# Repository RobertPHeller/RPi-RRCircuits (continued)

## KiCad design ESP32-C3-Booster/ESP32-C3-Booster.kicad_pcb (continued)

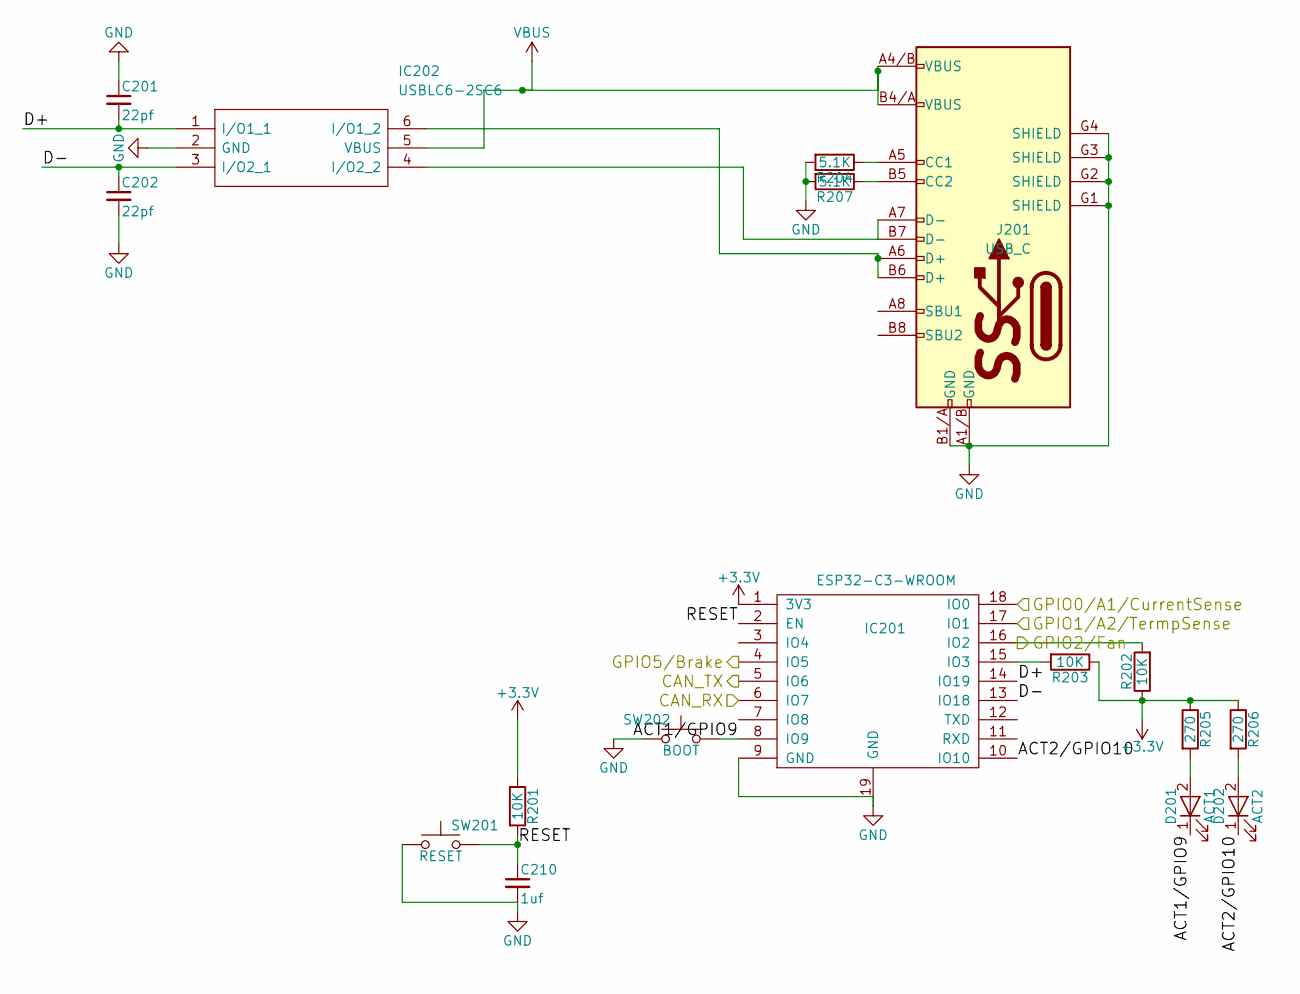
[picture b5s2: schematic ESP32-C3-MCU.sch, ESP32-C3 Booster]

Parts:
C201, C202: 22pf; C_0402; Mouser Part Number 187-CL05C220JB5NNND
C210: 1uf; C_0402; Mouser Part Number 80-C0402C101K8RAUTO
D201: ACT1; LED_0402; Mouser Part Number 710-150040GS73220
D202: ACT2; LED_0402; Mouser Part Number 710-150040SS73220
IC201: ESP32-C3-WROOM; Mouser Part Number 356-ESP32C3WROOM02N4
IC202: USBLC6-2SC6; SOT-23-6; Mouser Part Number 511-USBLC6-2SC6
J201: USB_C; GCT_USB4105-GF-A; Mouser Part Number 640-USB4105-GF-A-120
R201, R202, R203: 10K; R_0402; Mouser Part Number 603-RC0402JR-1310KL
R204, R207: 5.1K; R_0402; Mouser Part Number 71-CRCW0402-5.1K-E3
R205, R206: 270; R_0402; Mouser Part Number 754-RR0510P-271D
SW201: RESET; PTS647SM38SMTR2LFS; Mouser Part Number 611-PTS647SN70SMTR2L
SW202: BOOT; PTS647SM38SMTR2LFS; Mouser Part Number 611-PTS647SN70SMTR2L

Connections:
+3V3: IC201.1 (3V3), R201.1, R202.1, R203.1, R205.1, R206.1; also elsewhere on the board
/CAN Transeiver/CAN_RX: IC201.6 (IO7); also elsewhere on the board
/CAN Transeiver/CAN_TX: IC201.5 (IO6); also elsewhere on the board
/ESP32-C3 MCU/ACT1/GPIO9: D201.1 (K), IC201.8 (IO9), SW202.1
/ESP32-C3 MCU/ACT2/GPIO10: D202.1 (K), IC201.10 (IO10)
/ESP32-C3 MCU/D+: C201.2, IC201.14 (IO19), IC202.1 (I/O1_1)
/ESP32-C3 MCU/D-: C202.1, IC201.13 (IO18), IC202.3 (I/O2_1)
/ESP32-C3 MCU/GPIO0/A1/CurrentSense: IC201.18 (IO0); also elsewhere on the board
/ESP32-C3 MCU/GPIO1/A2/TermpSense: IC201.17 (IO1); also elsewhere on the board
/ESP32-C3 MCU/RESET: C210.1, IC201.2 (EN), R201.2, SW201.2
/Fan Controls/FAN_CONTROL: IC201.16 (IO2), R202.2; also elsewhere on the board
/OPS Driver/BRAKE: IC201.4 (IO5); also elsewhere on the board
GND: C201.1, C202.2, C210.2, IC201.9 (GND), IC201.19 (GND), IC202.2 (GND), J201.A1/B (GND), J201.B1/A (GND), J201.G1 (SHIELD), J201.G2 (SHIELD), J201.G3 (SHIELD), J201.G4 (SHIELD), R204.2, R207.2, SW201.1, SW202.2; also elsewhere on the board
unnamed: D201.2 (A), R205.2
unnamed: D202.2 (A), R206.2
unnamed: IC201.15 (IO3), R203.2
unnamed: IC202.4 (I/O2_2), J201.A7 (D-), J201.B7 (D-)
unnamed: IC202.6 (I/O1_2), J201.A6 (D+), J201.B6 (D+)
unnamed: J201.A5 (CC1), R204.1
unnamed: J201.B5 (CC2), R207.1
VBUS: IC202.5 (VBUS), J201.A4/B (VBUS), J201.B4/A (VBUS); also elsewhere on the board

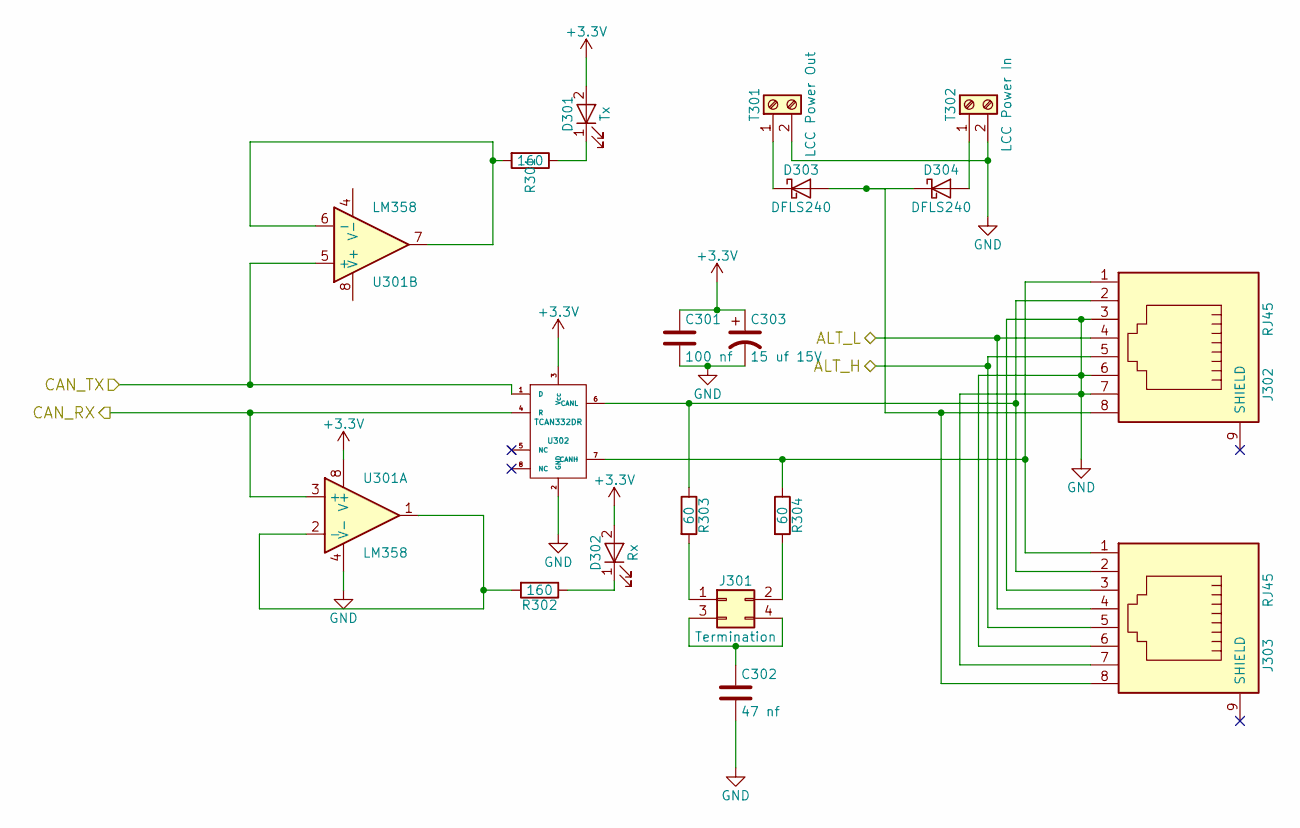
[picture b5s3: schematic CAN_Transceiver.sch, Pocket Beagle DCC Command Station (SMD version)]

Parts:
C301: 100 nf; C_0603; Mouser Part Number 603-CC603KPX7R9BB104
C302: 47 nf; C_0603; Mouser Part Number 963-GMK107BJ473KAHT
C303: 15 uf 15V; CP_Elec_4x5.8; Mouser Part Number 647-UUD1C150MCL
D301: Tx; LED_0603; Mouser Part Number 710-150060SS75000
D302: Rx; LED_0603; Mouser Part Number 710-150060YS75000
D303, D304: DFLS240; D_PowerDI-123; Mouser Part Number 621-DFLS240-7
J301: Termination; Pin_Header_Straight_2x02_Pitch2.54mm; Mouser Part Number 538-90131-0122
J302, J303: RJ45; RJ45_8N-S; Mouser Part Number 710-615008144221
R301, R302: 160; R_0603; Mouser Part Number 603-AC0603JR-07160RL
R303, R304: 60; R_1206; Mouser Part Number 71-CRCW120660R0KNAIF
T301: LCC Power Out; TerminalBlock_Pheonix_MPT-2.54mm_2pol; Mouser Part Number 651-1725656
T302: LCC Power In; TerminalBlock_Pheonix_MPT-2.54mm_2pol; Mouser Part Number 651-1725656
U301: LM358; SOIC-8_3.9x4.9mm_Pitch1.27mm; Mouser Part Number 595-LM358BIDR
U302: TCAN332DR; SOIC-8_3.9x4.9mm_Pitch1.27mm; Mouser Part Number 595-TCAN332DR

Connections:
+3V3: C301.1, C303.1, D301.2 (A), D302.2 (A), U301.8 (V+), U302.3 (Vcc); also elsewhere on the board
/CAN Transeiver/ALT_H: J302.5, J303.5; also elsewhere on the board
/CAN Transeiver/ALT_L: J302.4, J303.4; also elsewhere on the board
/CAN Transeiver/CAN_RX: U301.3 (+), U302.4 (R); also elsewhere on the board
/CAN Transeiver/CAN_TX: U301.5 (+), U302.1 (D); also elsewhere on the board
GND: C301.2, C302.2, C303.2, J302.3, J302.6, J302.7, J303.3, J303.6, J303.7, T301.2, T302.2, U301.4 (V-), U302.2 (GND); also elsewhere on the board
unnamed: C302.1, J301.3, J301.4
unnamed: D301.1 (K), R301.1
unnamed: D302.1 (K), R302.1
unnamed: D303.1 (K), T301.1
unnamed: D303.2 (A), D304.1 (K), J302.8, J303.8
unnamed: D304.2 (A), T302.1
unnamed: J301.1, R303.2
unnamed: J301.2, R304.2
unnamed: J302.1, J303.1, R304.1, U302.7 (CANH)
unnamed: J302.2, J303.2, R303.1, U302.6 (CANL)
unnamed: R301.2, U301.6 (-), U301.7
unnamed: R302.2, U301.1, U301.2 (-)

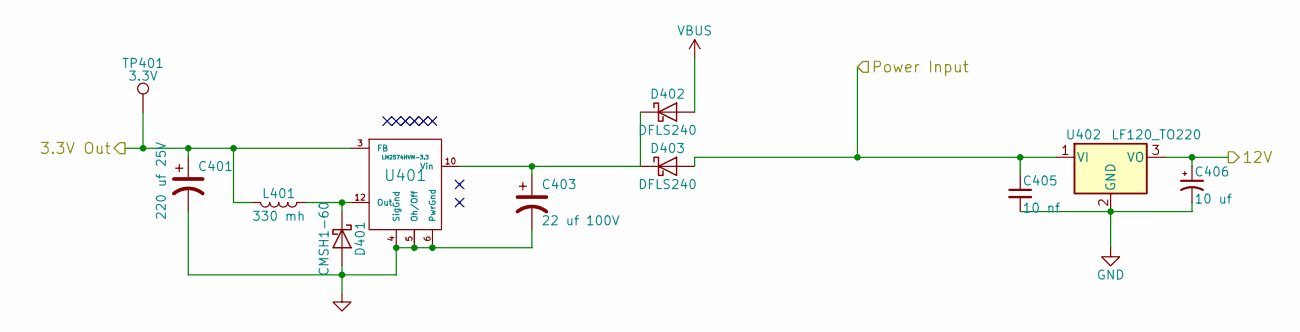
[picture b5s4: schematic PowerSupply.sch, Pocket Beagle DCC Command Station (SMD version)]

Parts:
C401: 220 uf 25V; CP_Elec_8x10; Mouser Part Number 647-UUX2A220MNL6GS
C403: 22 uf 100V; CP_Elec_8x10; Mouser Part Number 647-UWT1E221MNL1GS
C405: 10 nf; C_1206; Mouser Part Number 791-1206B103K500CT
C406: 10 uf; CP_Elec_5x5.3; Mouser Part Number 710-865230542002
D401: CMSH1-60; D_SMA; Mouser Part Number 610-CMSH1-60TR13
D402, D403: DFLS240; D_PowerDI-123; Mouser Part Number 621-DFLS240-7
L401: 330 mh; SRN1060; Mouser Part Number 652-SRN1060-331M
TP401: 3.3V; Measurement_Point_Round-SMD-Pad_Big
U401: LM2574HVM-3.3; SOIC-14_7.4x8.7mm_Pitch1.27mm; Mouser Part Number 926-LM2574MX33NOPB
U402: LF120_TO220; TO-252-2; Mouser Part Number 511-LF120ABDT-TR

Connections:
+3V3: C401.1, L401.2, TP401.1, U401.3 (FB); also elsewhere on the board
+12V: C406.1, U402.3 (VO); also elsewhere on the board
/Power Supply/Power Input: C405.1, D403.2 (A), U402.1 (VI); also elsewhere on the board
GND: C401.2, C403.2, C405.2, C406.2, D401.2 (A), U401.4 (SigGnd), U401.5 (Oh/Off), U401.6 (PwrGnd), U402.2 (GND); also elsewhere on the board
unnamed: C403.1, D402.1 (K), D403.1 (K), U401.10 (Vin)
unnamed: D401.1 (K), L401.1, U401.12 (Out)
VBUS: D402.2 (A); also elsewhere on the board

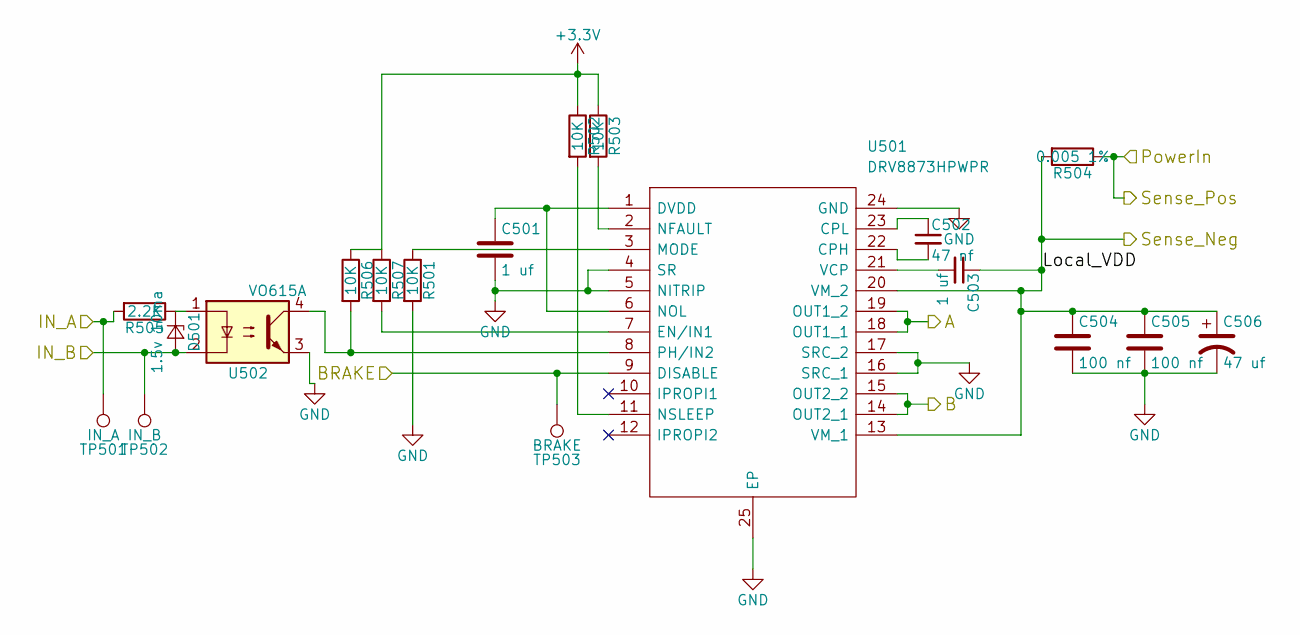
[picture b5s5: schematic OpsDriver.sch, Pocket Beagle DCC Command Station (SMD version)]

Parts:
C501, C503: 1 uf; C_0603; Mouser Part Number 963-GMK107AB7105KAHT
C502: 47 nf; C_0603; Mouser Part Number 963-GMK107BJ473KAHT
C504, C505: 100 nf; C_0603; Mouser Part Number 603-CC603KPX7R9BB104
C506: 47 uf; CP_Elec_6.3x5.3; Mouser Part Number 710-865080543009
D501: 1.5v 10ma; D_SOD-323; Mouser Part Number 610-CMDZ1L8TR
R501, R502, R503, R506, R507: 10K; R_0603; Mouser Part Number 279-CRGCQ0603F10K
R504: 0.005 1%; R_0612; Mouser Part Number 71-WSKW0612L5000FEA
R505: 2.2K; R_0603; Mouser Part Number 603-AC0603FR-072K2L
TP501: IN_A; Measurement_Point_Round-SMD-Pad_Big
TP502: IN_B; Measurement_Point_Round-SMD-Pad_Big
TP503: BRAKE; Measurement_Point_Round-SMD-Pad_Big
U501: DRV8873HPWPR; SOP65P640X120-25N; Mouser Part Number 595-DRV8873HPWPR
U502: VO615A; SO-4_7.6x3.6mm_Pitch2.54mm; Mouser Part Number 78-VO615A-7X017T

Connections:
+3V3: R502.1, R503.1, R506.1, R507.1; also elsewhere on the board
/CAN Transeiver/ALT_H: R505.2, TP501.1; also elsewhere on the board
/CAN Transeiver/ALT_L: D501.2 (A), TP502.1, U502.2; also elsewhere on the board
/OPS Driver/A: U501.18 (OUT1_1), U501.19 (OUT1_2); also elsewhere on the board
/OPS Driver/B: U501.14 (OUT2_1), U501.15 (OUT2_2); also elsewhere on the board
/OPS Driver/BRAKE: TP503.1, U501.9 (DISABLE); also elsewhere on the board
/OPS Driver/Sense_Neg: C503.1, C504.1, C505.1, C506.1, R504.2, U501.13 (VM_1), U501.20 (VM_2); also elsewhere on the board
/Power Supply/Power Input: R504.1; also elsewhere on the board
GND: C501.2, C504.2, C505.2, C506.2, R501.2, U501.4 (SR), U501.5 (NITRIP), U501.16 (SRC_1), U501.17 (SRC_2), U501.24 (GND), U501.25 (EP), U502.3; also elsewhere on the board
unnamed: C501.1, U501.1 (DVDD), U501.6 (NOL)
unnamed: C502.1, U501.23 (CPL)
unnamed: C502.2, U501.22 (CPH)
unnamed: C503.2, U501.21 (VCP)
unnamed: D501.1 (K), R505.1, U502.1
unnamed: R501.1, U501.3 (MODE)
unnamed: R502.2, U501.11 (NSLEEP)
unnamed: R503.2, U501.2 (NFAULT)
unnamed: R506.2, U501.8 (PH/IN2), U502.4
unnamed: R507.2, U501.7 (EN/IN1)

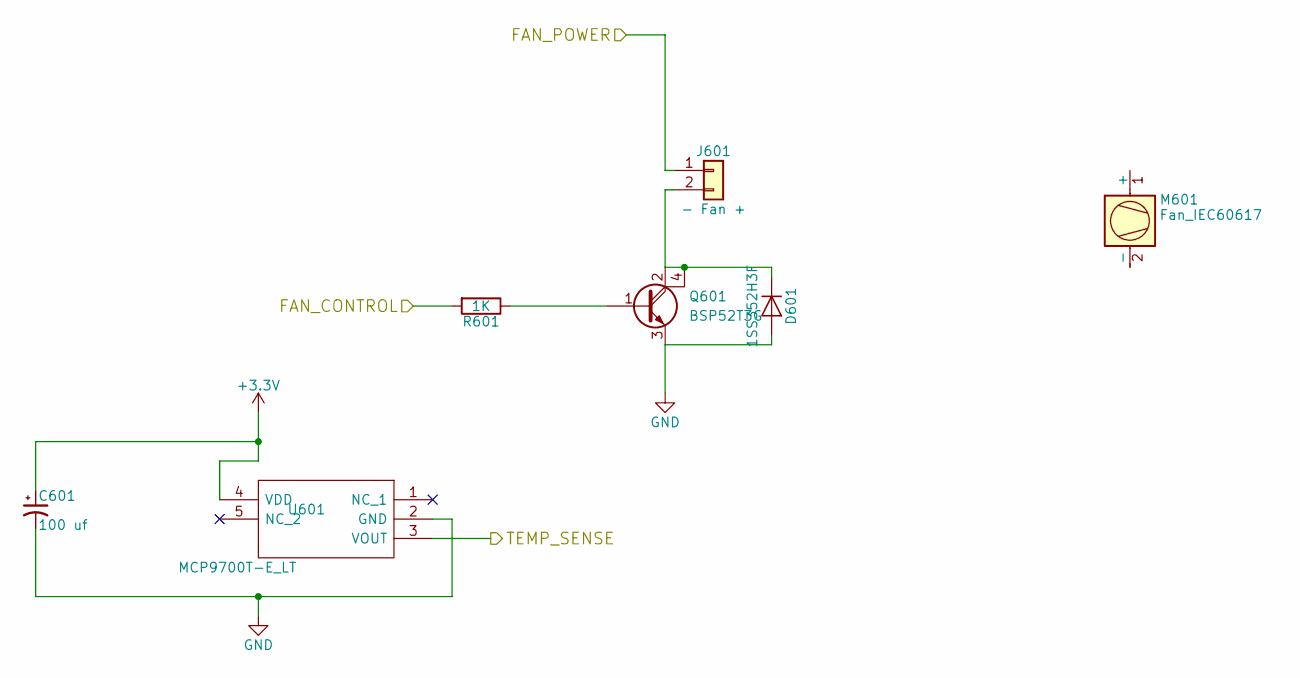
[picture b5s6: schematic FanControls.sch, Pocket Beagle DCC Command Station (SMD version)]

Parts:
C601: 100 uf; C_0603; Mouser Part Number 603-CC603KPX7R9BB104
D601: 1SS352H3F; D_SOD-323; Mouser Part Number 757-1SS352H3F
J601: - Fan +; Pin_Header_Straight_1x02_Pitch2.54mm; Mouser Part Number 538-42375-1855
M601: Fan_IEC60617; 25mmFanMount; Mouser Part Number 490-CFM2510B1100-218
Q601: BSP52T3G; SOT-223; Mouser Part Number 863-BSP52T3G
R601: 1K; R_0603; Mouser Part Number 279-CRGCQ0603F1K0
U601: MCP9700T-E_LT; SOT65P210X110-5N; Mouser Part Number 579-MCP9700T-E/LT

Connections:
+3V3: C601.1, U601.4 (VDD); also elsewhere on the board
+12V: J601.1; also elsewhere on the board
/ESP32-C3 MCU/GPIO1/A2/TermpSense: U601.3 (VOUT); also elsewhere on the board
/Fan Controls/FAN_CONTROL: R601.2; also elsewhere on the board
GND: C601.2, D601.2 (A), Q601.3 (E), U601.2 (GND); also elsewhere on the board
unnamed: D601.1 (K), J601.2, Q601.2 (C), Q601.4 (C2)
unnamed: Q601.1 (B), R601.1

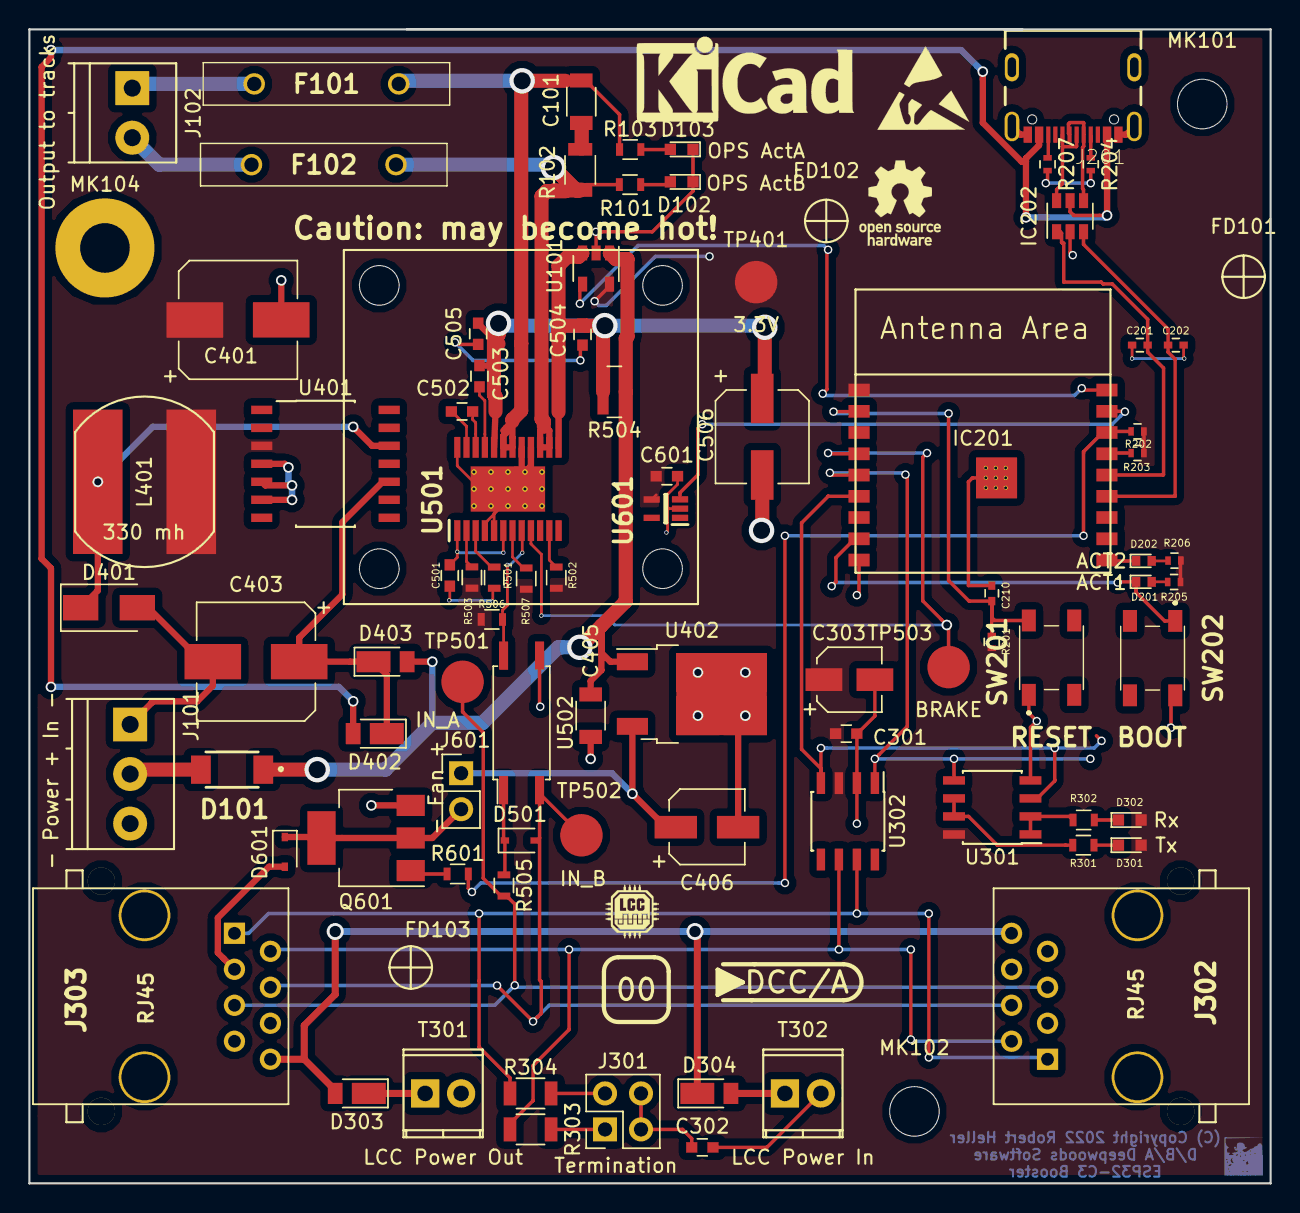
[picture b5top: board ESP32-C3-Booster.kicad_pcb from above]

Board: 2 copper layers, 87.6 x 81.5 mm, 90 parts (0 on the bottom side), 60 nets.

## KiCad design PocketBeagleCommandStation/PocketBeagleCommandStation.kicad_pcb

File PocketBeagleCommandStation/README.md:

# PocketBeagleCommandStation

Through hole version of the PocketBeagle LCC/DCC Command Station. This is a
DCC command station that is a LCC node. It implements the OpenLCB train
protocol node over LCC and converts that to DCC commands. It includes a
booster and puts the DCC signal on the LCC bus (pins 4 and 5). It implements a
programming track and implements Railcom. The Command Station uses a
PocketBeagle as the processing element and uses the PRUs (Programmable
Realtime Units) to generate the DCC signal. (See
[PocketBeagleCommandStation_SMD](https://github.com/RobertPHeller/RPi-RRCircuits/tree/master/PocketBeagleCommandStation_SMD)
for a SMD version.)

* [Mouser Cart](https://www.mouser.com/ProjectManager/ProjectDetail.aspx?AccessID=514917dd80)
* [Schematic PDF](https://github.com/RobertPHeller/RPi-RRCircuits/blob/master/PocketBeagleCommandStation/PocketBeagleCommandStation.pdf)
* [Board Rendering](https://github.com/RobertPHeller/RPi-RRCircuits/blob/master/PocketBeagleCommandStation/PocketBeagleCommandStation.png)
* [Node Software](https://github.com/RobertPHeller/RPi-RRCircuits/tree/master/BBBCommandStationOpenMRN)
* [Kit Booklet](https://github.com/RobertPHeller/RPi-RRCircuits/blob/master/PocketBeagleCommandStation/KitBooklet.pdf)
* Heat sink files:
  * [Main panel](https://github.com/RobertPHeller/RPi-RRCircuits/blob/master/PocketBeagleCommandStation/HeatSinkMainPanel.pdf)
  * [Fin 1](https://github.com/RobertPHeller/RPi-RRCircuits/blob/master/PocketBeagleCommandStation/HeatSinkFin1Panel.pdf)
  * [Fin 2](https://github.com/RobertPHeller/RPi-RRCircuits/blob/master/PocketBeagleCommandStation/HeatSinkFin2Panel.pdf)
  * [Cut page 1:1 (SVG)](https://github.com/RobertPHeller/RPi-RRCircuits/blob/master/PocketBeagleCommandStation/HeatSinkLaserCutPage-nocps-cutsonly.svg)
  * [Cut and bend 1:1 (SVG)](https://github.com/RobertPHeller/RPi-RRCircuits/blob/master/PocketBeagleCommandStation/HeatSinkLaserCutPage-nocps.svg)
  * [Cut and bend 1:1 (SVG, with center points)](https://github.com/RobertPHeller/RPi-RRCircuits/blob/master/PocketBeagleCommandStation/HeatSinkLaserCutPage.svg)
  * [FreeCAD Python script](https://github.com/RobertPHeller/RPi-RRCircuits/blob/master/PocketBeagleCommandStation/HeatSink.py)

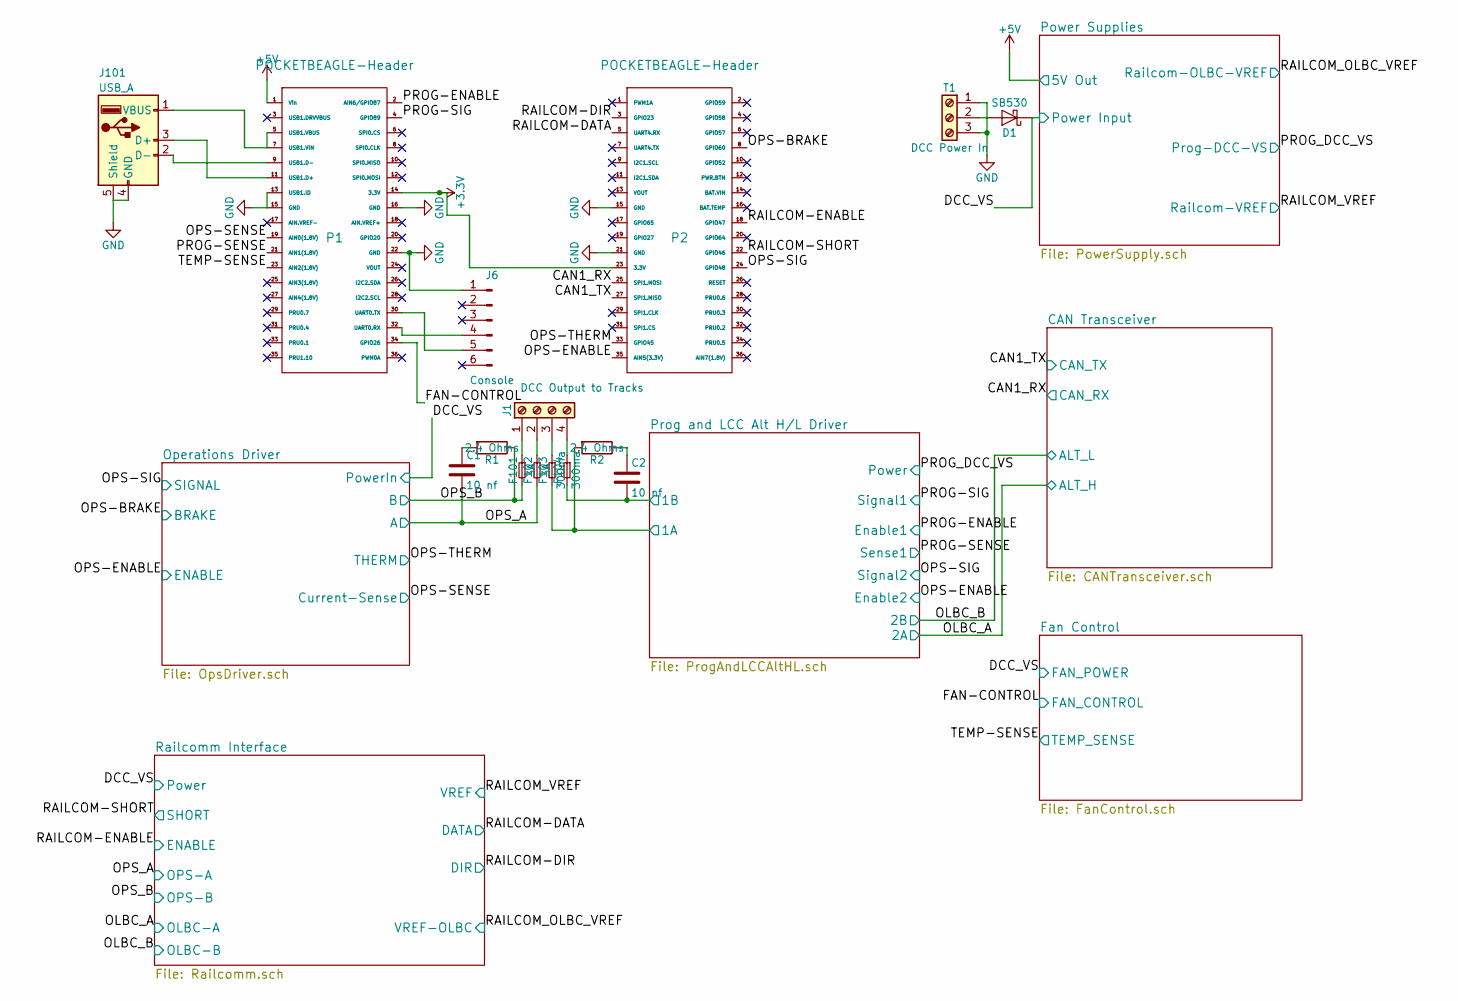
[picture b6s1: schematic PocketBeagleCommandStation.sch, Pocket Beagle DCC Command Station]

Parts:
C1, C2: 10 nf; C_Rect_L4.0mm_W2.5mm_P2.50mm; Mouser Part Number 75-1C10Z5U103M100B
D1: SB530; D_DO-201AD_P12.70mm_Horizontal; Mouser Part Number 625-SB530-E3
F101, F102: 3A; Fuse_BelFuse_0ZRE0033FF_L11.4mm_W3.8mm; Mouser Part Number 530-0ZRB0300FF1A
F103, F104: 300ma; Fuse_Bourns_MF-RG300; Mouser Part Number 530-0ZRC0030FF1E
J1: DCC Output to Tracks; TerminalBlock_Pheonix_PT-3.5mm_4pol; Mouser Part Number 651-5442264
J6: Console; Pin_Header_Straight_1x06_Pitch2.54mm; Mouser Part Number 523-G800W302018EU
J101: USB_A; USB-A-UPRIGHT; Mouser Part Number 710-614004184726
P1, P2: POCKETBEAGLE-Header; Socket_Strip_Straight_2x18_Pitch2.54mm; Mouser Part Number 517-929975-01-18-RK
R1, R2: 2.4 Ohms; R_Axial_DIN0204_L3.6mm_D1.6mm_P2.54mm_Vertical; Mouser Part Number 603-CFR-25JB-52-2R4
T1: DCC Power In; TerminalBlock_Pheonix_PT-3.5mm_3pol; Mouser Part Number 651-5442251

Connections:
+3V3: P1.14 (3.3V), P2.23 (3.3V); also elsewhere on the board
+5V: P1.1 (Vin); also elsewhere on the board
/CAN1_RX: P2.25 (SPI1.MOSI); also elsewhere on the board
/CAN1_TX: P2.27 (SPI1.MISO); also elsewhere on the board
/DCC_VS: D1.1 (K); also elsewhere on the board
/FAN-CONTROL: P1.34 (GPIO26); also elsewhere on the board
/OPS-BRAKE: P2.8 (GPIO60); also elsewhere on the board
/OPS-ENABLE: P2.35 (AIN5(3.3V)); also elsewhere on the board
/OPS-SENSE: P1.19 (AIN0(1.8V)); also elsewhere on the board
/OPS-SIG: P2.24 (GPIO48); also elsewhere on the board
/OPS-THERM: P2.33 (GPIO45); also elsewhere on the board
/OPS_A: C1.2, F102.2; also elsewhere on the board
/OPS_B: F101.2, R1.1; also elsewhere on the board
/PROG-ENABLE: P1.2 (AIN6/GPIO87); also elsewhere on the board
/PROG-SENSE: P1.21 (AIN1(1.8V)); also elsewhere on the board
/PROG-SIG: P1.4 (GPIO89); also elsewhere on the board
/Prog and LCC Alt H/L Driver/1A: F103.2, R2.2; also elsewhere on the board
/Prog and LCC Alt H/L Driver/1B: C2.2, F104.2; also elsewhere on the board
/RAILCOM-DATA: P2.5 (UART4.RX); also elsewhere on the board
/RAILCOM-DIR: P2.3 (GPIO23); also elsewhere on the board
/RAILCOM-ENABLE: P2.18 (GPIO47); also elsewhere on the board
/RAILCOM-SHORT: P2.22 (GPIO46); also elsewhere on the board
/TEMP-SENSE: P1.23 (AIN2(1.8V)); also elsewhere on the board
GND: J6.1, J101.4 (GND), J101.5 (Shield), P1.13 (USB1.ID), P1.15 (GND), P1.16 (GND), P1.22 (GND), P2.15 (GND), P2.21 (GND), T1.1, T1.3; also elsewhere on the board
unnamed: C1.1, R1.2
unnamed: C2.1, R2.1
unnamed: D1.2 (A), T1.2
unnamed: F101.1, J1.1
unnamed: F102.1, J1.2
unnamed: F103.1, J1.3
unnamed: F104.1, J1.4
unnamed: J6.4, P1.32 (UART0.RX)
unnamed: J6.5, P1.30 (UART0.TX)
unnamed: J101.1 (VBUS), P1.5 (USB1.VBUS), P1.7 (USB1.VIN)
unnamed: J101.2 (D-), P1.9 (USB1.D-)
unnamed: J101.3 (D+), P1.11 (USB1.D+)

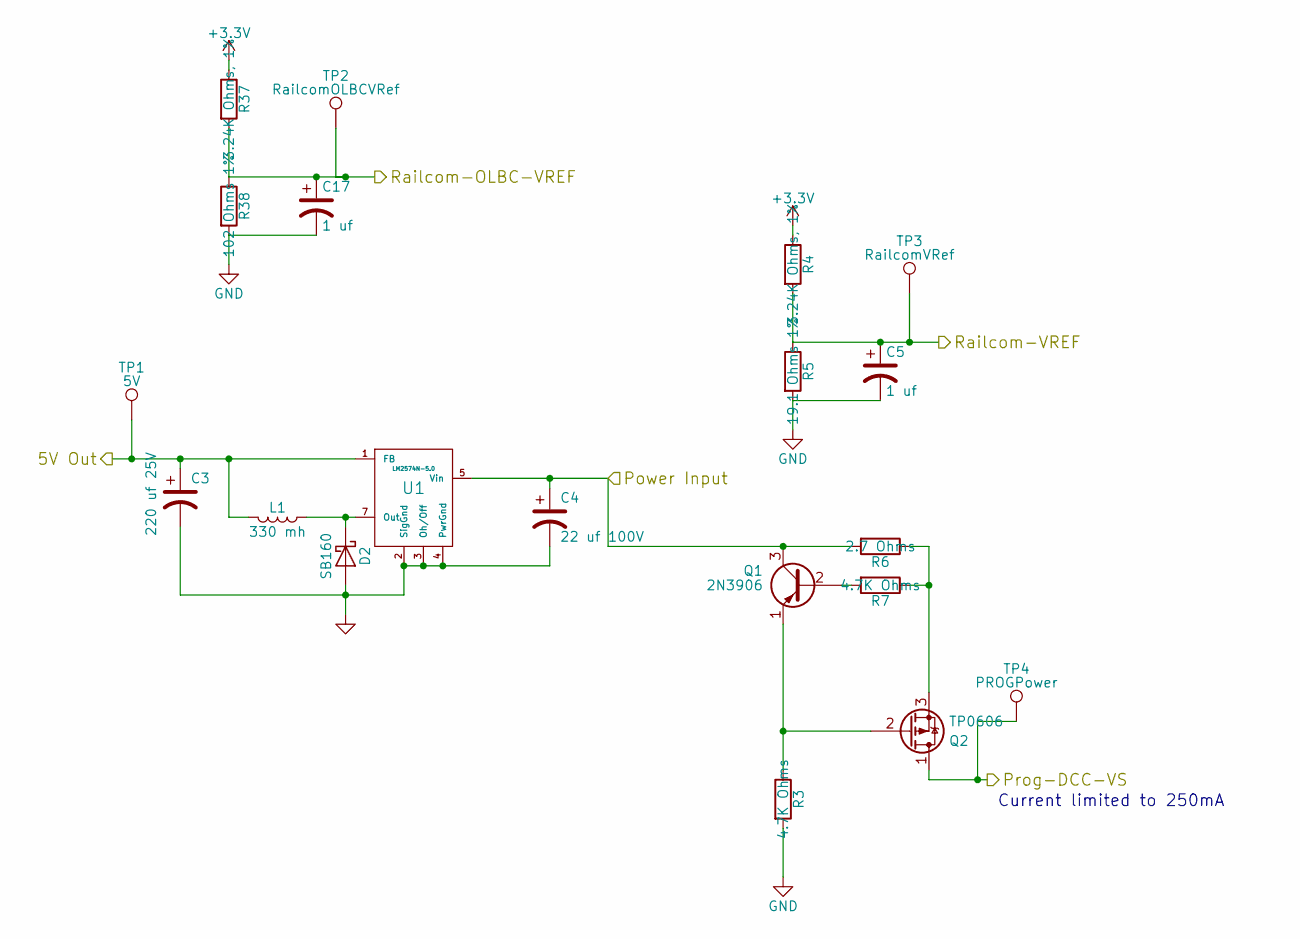
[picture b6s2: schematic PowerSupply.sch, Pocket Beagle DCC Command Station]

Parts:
C3: 220 uf 25V; CP_Radial_D8.0mm_P3.50mm; Mouser Part Number 710-860080474010
C4: 22 uf 100V; CP_Radial_D8.0mm_P3.50mm; Mouser Part Number 667-ECA-1VM220I
C5, C17: 1 uf; CP_Radial_D5.0mm_P2.50mm; Mouser Part Number 810-FG18X5R1H105KRT6
D2: SB160; D_DO-41_SOD81_P7.62mm_Horizontal; Mouser Part Number 750-SB160E-G
L1: 330 mh; PE-LowProfile; Mouser Part Number 673-PE-52627NL
Q1: 2N3906; TO-92_Molded_Narrow; Mouser Part Number 750-2N3906-G
Q2: TP0606; TO-92_Molded_Narrow; Mouser Part Number 689-TP0606N3-G
R3, R7: 4.7K Ohms; R_Axial_DIN0204_L3.6mm_D1.6mm_P2.54mm_Vertical; Mouser Part Number 603-CFR-12JT-52-4K7
R4: 3.24K Ohms, 1%; R_Axial_DIN0204_L3.6mm_D1.6mm_P2.54mm_Vertical; Mouser Part Number 603-MFR-25FRF52-3K24
R5: 19.1 Ohms 1%; R_Axial_DIN0204_L3.6mm_D1.6mm_P2.54mm_Vertical; Mouser Part Number 603-MFR-25FBF52-19R1
R6: 2.7 Ohms; R_Axial_DIN0204_L3.6mm_D1.6mm_P2.54mm_Vertical; Mouser Part Number 603-CFR-25JR-52-2R7
R37: 3.24K Ohms, 1%; R_Axial_DIN0204_L3.6mm_D1.6mm_P1.90mm_Vertical; Mouser Part Number 603-MFR-25FRF52-3K24
R38: 102 Ohms 1%; R_Axial_DIN0204_L3.6mm_D1.6mm_P1.90mm_Vertical; Mouser Part Number 603-MFR-25FBF52-102R
TP1: 5V; Measurement_Point_Round-TH_Small
TP2: RailcomOLBCVRef; Measurement_Point_Round-TH_Small
TP3: RailcomVRef; Measurement_Point_Round-TH_Small
TP4: PROGPower; Measurement_Point_Round-TH_Small
U1: LM2574N-5.0; DIP-8_W7.62mm; Mouser Part Number 926-LM2574N-5.0/NOPB

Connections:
+3V3: R4.1, R37.1; also elsewhere on the board
+5V: C3.1, L1.2, TP1.1, U1.1 (FB); also elsewhere on the board
/DCC_VS: C4.1, Q1.3 (C), R6.2, U1.5 (Vin); also elsewhere on the board
/PROG_DCC_VS: Q2.1 (D), TP4.1; also elsewhere on the board
/RAILCOM_OLBC_VREF: C17.1, R37.2, R38.1, TP2.1; also elsewhere on the board
/RAILCOM_VREF: C5.1, R4.2, R5.1, TP3.1; also elsewhere on the board
GND: C3.2, C4.2, C5.2, C17.2, D2.2 (A), R3.2, R5.2, R38.2, U1.2 (SigGnd), U1.3 (Oh/Off), U1.4 (PwrGnd); also elsewhere on the board
unnamed: D2.1 (K), L1.1, U1.7 (Out)
unnamed: Q1.1 (E), Q2.2 (G), R3.1
unnamed: Q1.2 (B), R7.2
unnamed: Q2.3 (S), R6.1, R7.1

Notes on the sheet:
Current limited to 250mA

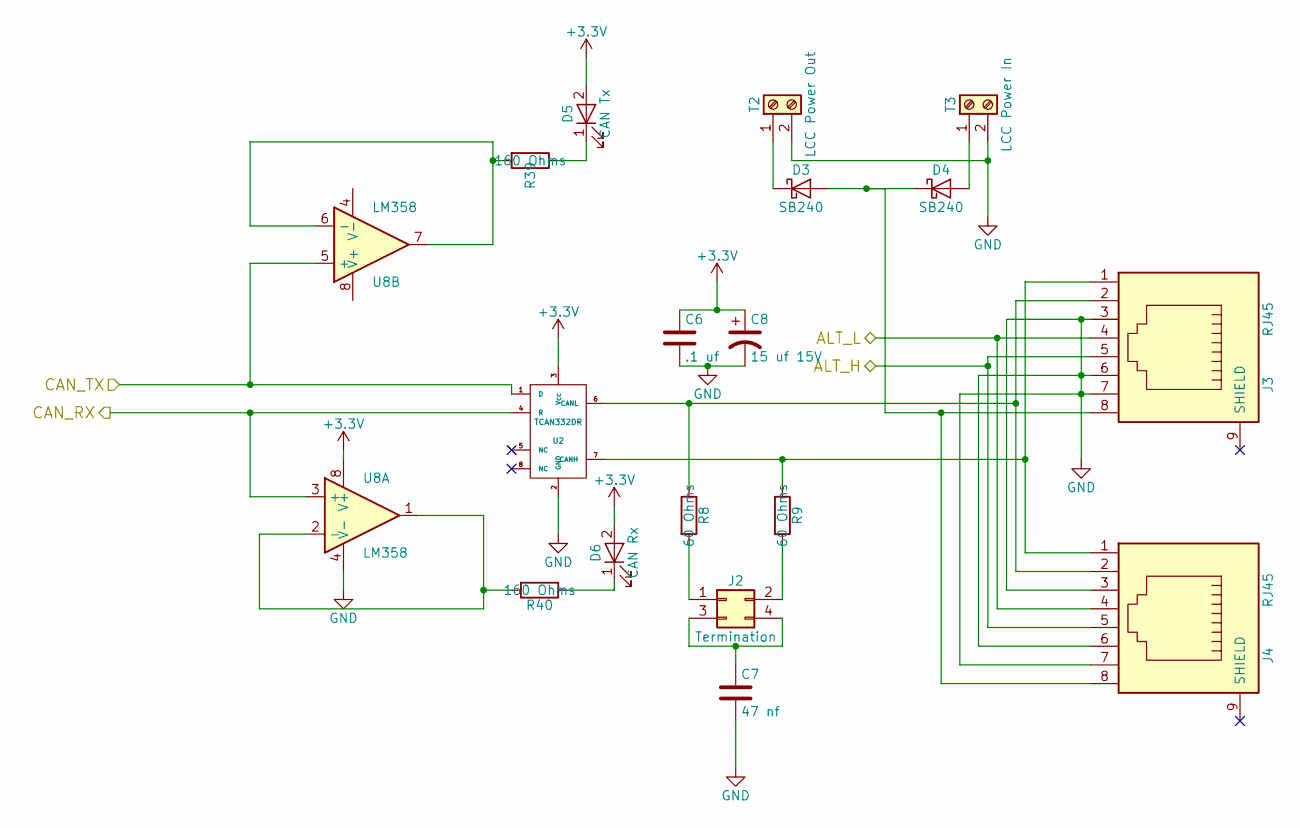
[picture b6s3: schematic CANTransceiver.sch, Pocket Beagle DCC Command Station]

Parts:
C6: .1 uf; C_Rect_L4.0mm_W2.5mm_P2.50mm; Mouser Part Number 594-K104Z15Y5VF5TL2
C7: 47 nf; C_Rect_L4.0mm_W2.5mm_P2.50mm; Mouser Part Number 594-K473K15X7RF5TL2
C8: 15 uf 15V; CP_Radial_D6.3mm_P2.50mm; Mouser Part Number 710-860080773002
D3, D4: SB240; D_DO-15_P10.16mm_Horizontal; Mouser Part Number 625-SB240-E3/73
D5: CAN Tx; LED_D3.0mm; Mouser Part Number 710-151031SS04000
D6: CAN Rx; LED_D3.0mm; Mouser Part Number 710-151033YS03000
J2: Termination; Pin_Header_Straight_2x02_Pitch2.54mm; Mouser Part Number 649-1012938190402BLF
J3, J4: RJ45; RJ45_8N-S; Mouser Part Number 710-615008144221
R8, R9: 60 Ohms; R_Axial_DIN0204_L3.6mm_D1.6mm_P2.54mm_Vertical; Mouser Part Number 603-RSF2WSJT-52-60R
R39, R40: 160 Ohms; R_Axial_DIN0204_L3.6mm_D1.6mm_P1.90mm_Vertical; Mouser Part Number 603-CFR-25JB-52-160R
T2: LCC Power Out; TerminalBlock_Pheonix_MPT-2.54mm_2pol; Mouser Part Number 651-1725656
T3: LCC Power In; TerminalBlock_Pheonix_MPT-2.54mm_2pol; Mouser Part Number 651-1725656
U2: TCAN332DR; SOIC-8-1EP_3.9x4.9mm_Pitch1.27mm; Mouser Part Number 595-TCAN332DR
U8: LM358; DIP-8_W7.62mm; Mouser Part Number 595-LM358AP

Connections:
+3V3: C6.1, C8.1, D5.2 (A), D6.2 (A), U2.3 (Vcc), U8.8 (V+); also elsewhere on the board
/CAN1_RX: U2.4 (R), U8.3 (+); also elsewhere on the board
/CAN1_TX: U2.1 (D), U8.5 (+); also elsewhere on the board
/OLBC_A: J3.5, J4.5; also elsewhere on the board
/OLBC_B: J3.4, J4.4; also elsewhere on the board
GND: C6.2, C7.2, C8.2, J3.3, J3.6, J3.7, J4.3, J4.6, J4.7, T2.2, T3.2, U2.2 (GND), U8.4 (V-); also elsewhere on the board
unnamed: C7.1, J2.3, J2.4
unnamed: D3.1 (K), T2.1
unnamed: D3.2 (A), D4.1 (K), J3.8, J4.8
unnamed: D4.2 (A), T3.1
unnamed: D5.1 (K), R39.1
unnamed: D6.1 (K), R40.1
unnamed: J2.1, R8.2
unnamed: J2.2, R9.2
unnamed: J3.1, J4.1, R9.1, U2.7 (CANH)
unnamed: J3.2, J4.2, R8.1, U2.6 (CANL)
unnamed: R39.2, U8.6 (-), U8.7
unnamed: R40.2, U8.1, U8.2 (-)

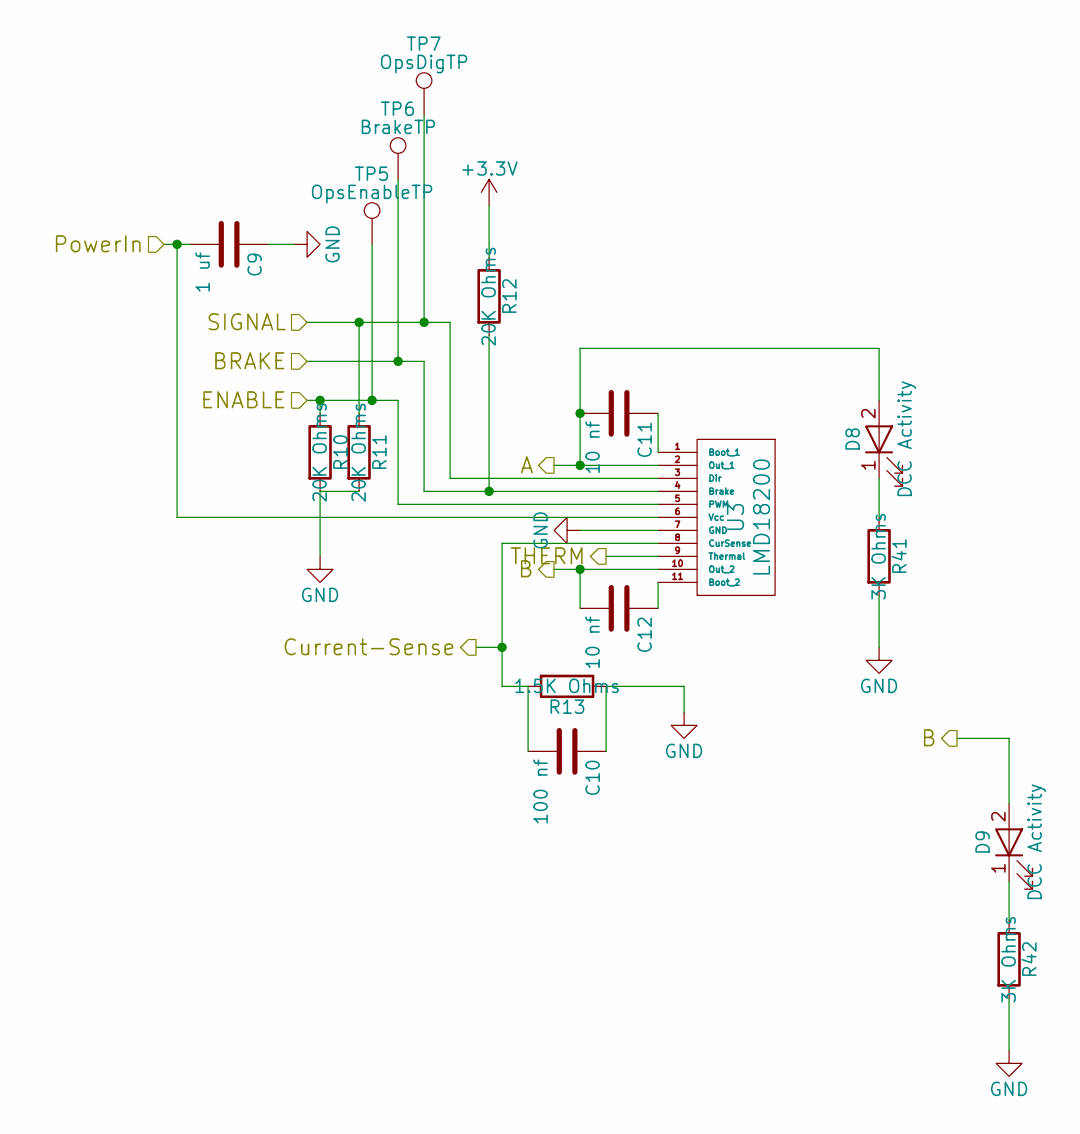
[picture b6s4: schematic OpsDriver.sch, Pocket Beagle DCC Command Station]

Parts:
C9: 1 uf; C_Rect_L7.0mm_W2.0mm_P5.00mm; Mouser Part Number 810-FG18X5R1H105KRT6
C10: 100 nf; C_Rect_L4.0mm_W2.5mm_P2.50mm; Mouser Part Number 594-K104Z15Y5VF5TL2
C11, C12: 10 nf; C_Rect_L4.0mm_W2.5mm_P2.50mm; Mouser Part Number 75-1C10Z5U103M100B
D8: DCC Activity; LED_D3.0mm; Mouser Part Number 710-151031VS06000
D9: DCC Activity; LED_D3.0mm; Mouser Part Number 710-151031SS06000
R10, R11, R12: 20K Ohms; R_Axial_DIN0204_L3.6mm_D1.6mm_P2.54mm_Vertical; Mouser Part Number 603-MFR-12FTF52-20K
R13: 1.5K Ohms; R_Axial_DIN0204_L3.6mm_D1.6mm_P2.54mm_Vertical; Mouser Part Number 279-CFR25J1K5
R41, R42: 3K Ohms; R_Axial_DIN0204_L3.6mm_D1.6mm_P1.90mm_Vertical; Mouser Part Number 660-MF1/4LCT52R302G
TP5: OpsEnableTP; Measurement_Point_Round-TH_Small
TP6: BrakeTP; Measurement_Point_Round-TH_Small
TP7: OpsDigTP; Measurement_Point_Round-TH_Small
U3: LMD18200; TO220_11PIN_VERT; Mouser Part Number 926-LMD18200T/NOPB

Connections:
+3V3: R12.1; also elsewhere on the board
/DCC_VS: C9.2, U3.6 (Vcc); also elsewhere on the board
/OPS-BRAKE: R12.2, TP6.1, U3.4 (Brake); also elsewhere on the board
/OPS-ENABLE: R10.1, TP5.1, U3.5 (PWM); also elsewhere on the board
/OPS-SENSE: C10.2, R13.2, U3.8 (CurSense); also elsewhere on the board
/OPS-SIG: R11.1, TP7.1, U3.3 (Dir); also elsewhere on the board
/OPS-THERM: U3.9 (Thermal); also elsewhere on the board
/OPS_A: C11.2, D8.2 (A), U3.2 (Out_1); also elsewhere on the board
/OPS_B: C12.2, D9.2 (A), U3.10 (Out_2); also elsewhere on the board
GND: C9.1, C10.1, R10.2, R11.2, R13.1, R41.2, R42.2, U3.7 (GND); also elsewhere on the board
unnamed: C11.1, U3.1 (Boot_1)
unnamed: C12.1, U3.11 (Boot_2)
unnamed: D8.1 (K), R41.1
unnamed: D9.1 (K), R42.1
